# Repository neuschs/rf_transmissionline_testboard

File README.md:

# Transmission Line Testboard 
A simple PCB designed according to JLC23313 layer stackup 

There are many different impedance controlled transmission lines, with the most common Zo = 50 Ohm / Zdiff = 100 Ohm

- Coplanar Waveguide (Single / Differential)

- Microstrip (Single / Differential)

- Stripline (Single / Differential):

  A impedance controlled Via and a set of differential vias gets the stripline up to a coplanar waveguide to the sma connectors
  For a future version vertical SMA mounts would be better to avoid vias where the goal was to proof impedance control calculations.
 
- 90° track (as Coplanar Waveguide)

  I put this track on the pcb to measure the effects of 90° bends on transmission lines.

- 50% top 50% bottom track connected by 50 ohm via:
 to verify impedance of via if the coplanar waveguide calculations are all correct.

# Parameters @ production:

Base Material: FR-4\
Layers: 4\
Dimension: 100 mm* 100 mm\
PCB Qty: 5\
Product Type: Industrial/Consumer electronics\
Different Design: 1\
Delivery Fomat: Single PCB\
PCB Thickness: 1.6\
Impedance: yes JLC2313\
PCB Color: Green\
Silkscreen: White\
Surface Finish: HASL(with lead)\
Deburring/Edge rounding: No\
Outer Copper Weight: 1\
Inner Copper Weight: 0.5\
Gold Fingers: No\
Flying Probe Test: Fully Test\
Castellated Holes: no\
Remove Order Number: Yes\
Min hole size/diameter:0.2/0.45mm\
4-Wire Kelvin Test:No\
Material Type:FR4-Standard Tg 130-140C\
Paper between PCBs:No\
Appearance Quality:IPC Class 2 Standard\
Confirm Production file:Yes

# Credits
I mostly calculated the values with https://www.maartenbaert.be/alterpcb/tlinesim/ which has quite accurate interpretation of all different parts of the pcb.
After comparison, this tool was nearly exactly the same to the manufacturer (JLCPCB) regarding a 50 Ohm transmission line with JLC2313 stackup.

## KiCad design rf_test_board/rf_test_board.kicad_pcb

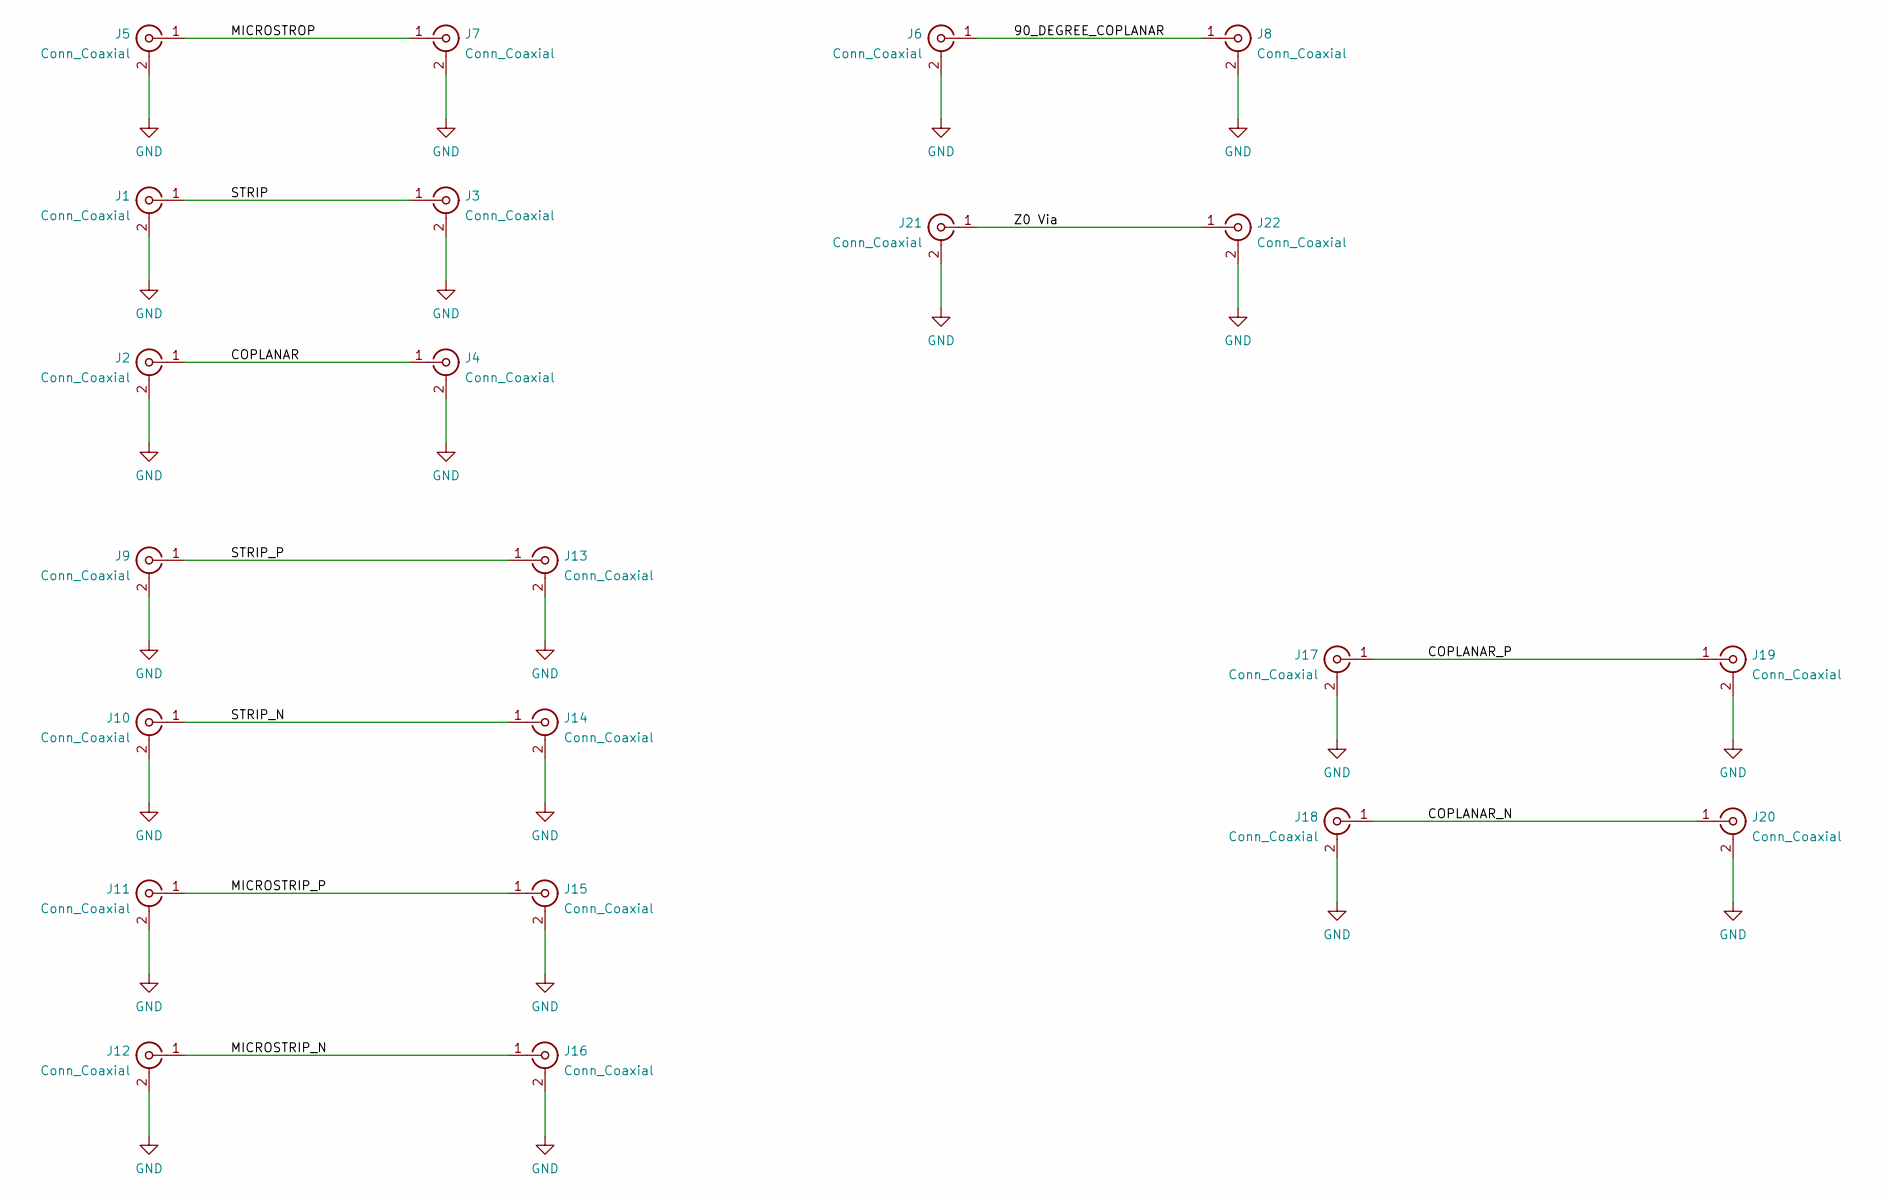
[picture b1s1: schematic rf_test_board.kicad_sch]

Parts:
J1, J2, J3, J4, J5, J6, J7, J8, J9, J10, J11, J12, J13, J14, J15, J16, J17, J18, J19, J20, J21, J22: Conn_Coaxial; SMA_Molex_73251-1153_EdgeMount_Horizontal

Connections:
/90_DEGREE_COPLANAR: J6.1 (In), J8.1 (In)
/COPLANAR: J2.1 (In), J4.1 (In)
/COPLANAR_N: J18.1 (In), J20.1 (In)
/COPLANAR_P: J17.1 (In), J19.1 (In)
/MICROSTRIP_N: J12.1 (In), J16.1 (In)
/MICROSTRIP_P: J11.1 (In), J15.1 (In)
/MICROSTROP: J5.1 (In), J7.1 (In)
/STRIP: J1.1 (In), J3.1 (In)
/STRIP_N: J10.1 (In), J14.1 (In)
/STRIP_P: J9.1 (In), J13.1 (In)
/Z0 Via: J21.1 (In), J22.1 (In)
GND: J1.2 (Ext), J2.2 (Ext), J3.2 (Ext), J4.2 (Ext), J5.2 (Ext), J6.2 (Ext), J7.2 (Ext), J8.2 (Ext), J9.2 (Ext), J10.2 (Ext), J11.2 (Ext), J12.2 (Ext), J13.2 (Ext), J14.2 (Ext), J15.2 (Ext), J16.2 (Ext), J17.2 (Ext), J18.2 (Ext), J19.2 (Ext), J20.2 (Ext), J21.2 (Ext), J22.2 (Ext)

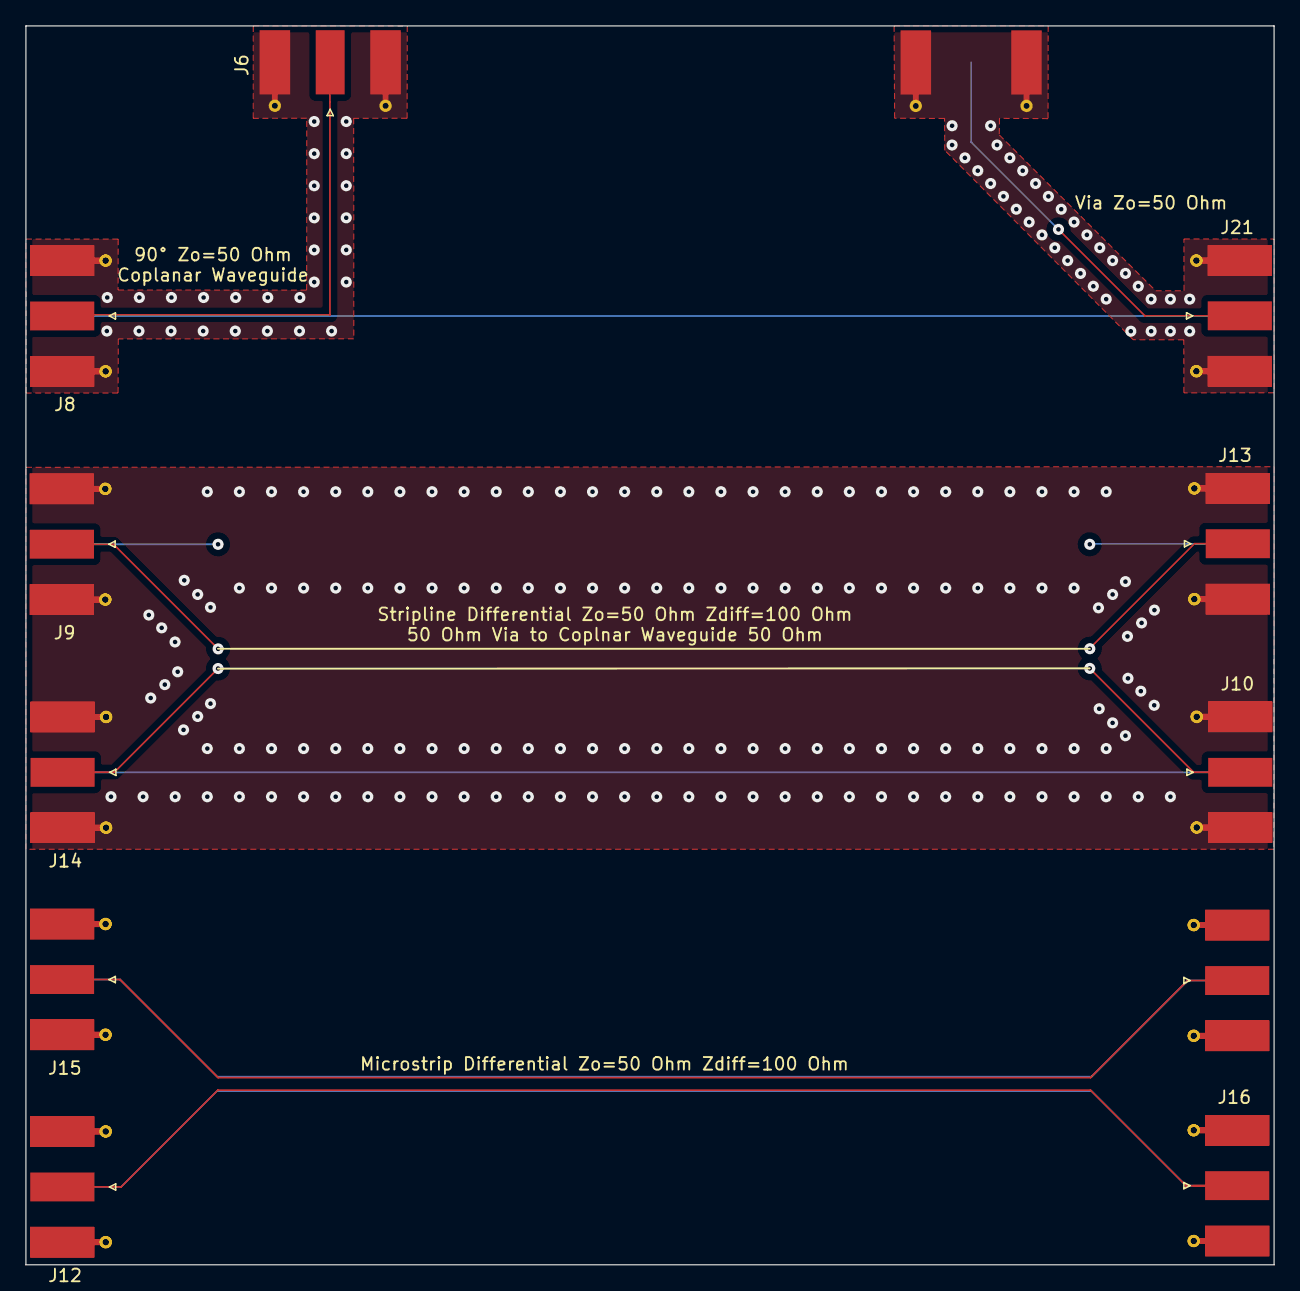
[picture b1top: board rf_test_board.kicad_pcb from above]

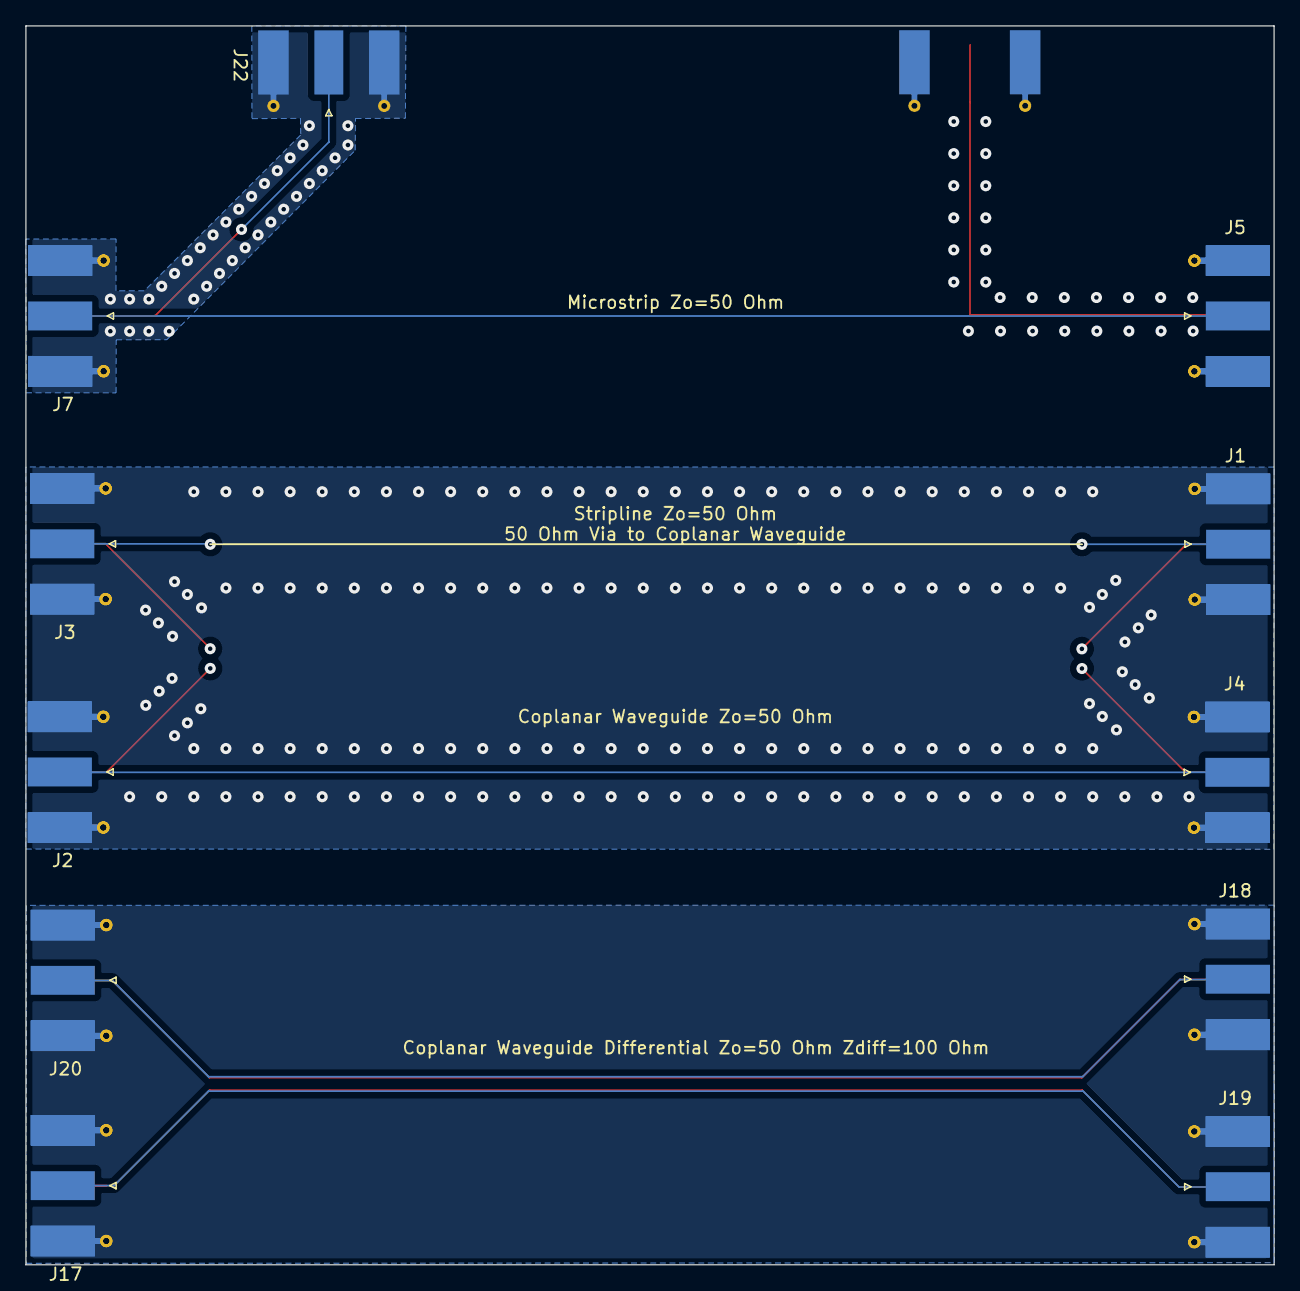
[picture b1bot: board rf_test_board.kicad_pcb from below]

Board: 4 copper layers, 98.8 x 98.0 mm, 22 parts (11 on the bottom side), 12 nets.

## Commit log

2022-06-09 version one of the rf test board
